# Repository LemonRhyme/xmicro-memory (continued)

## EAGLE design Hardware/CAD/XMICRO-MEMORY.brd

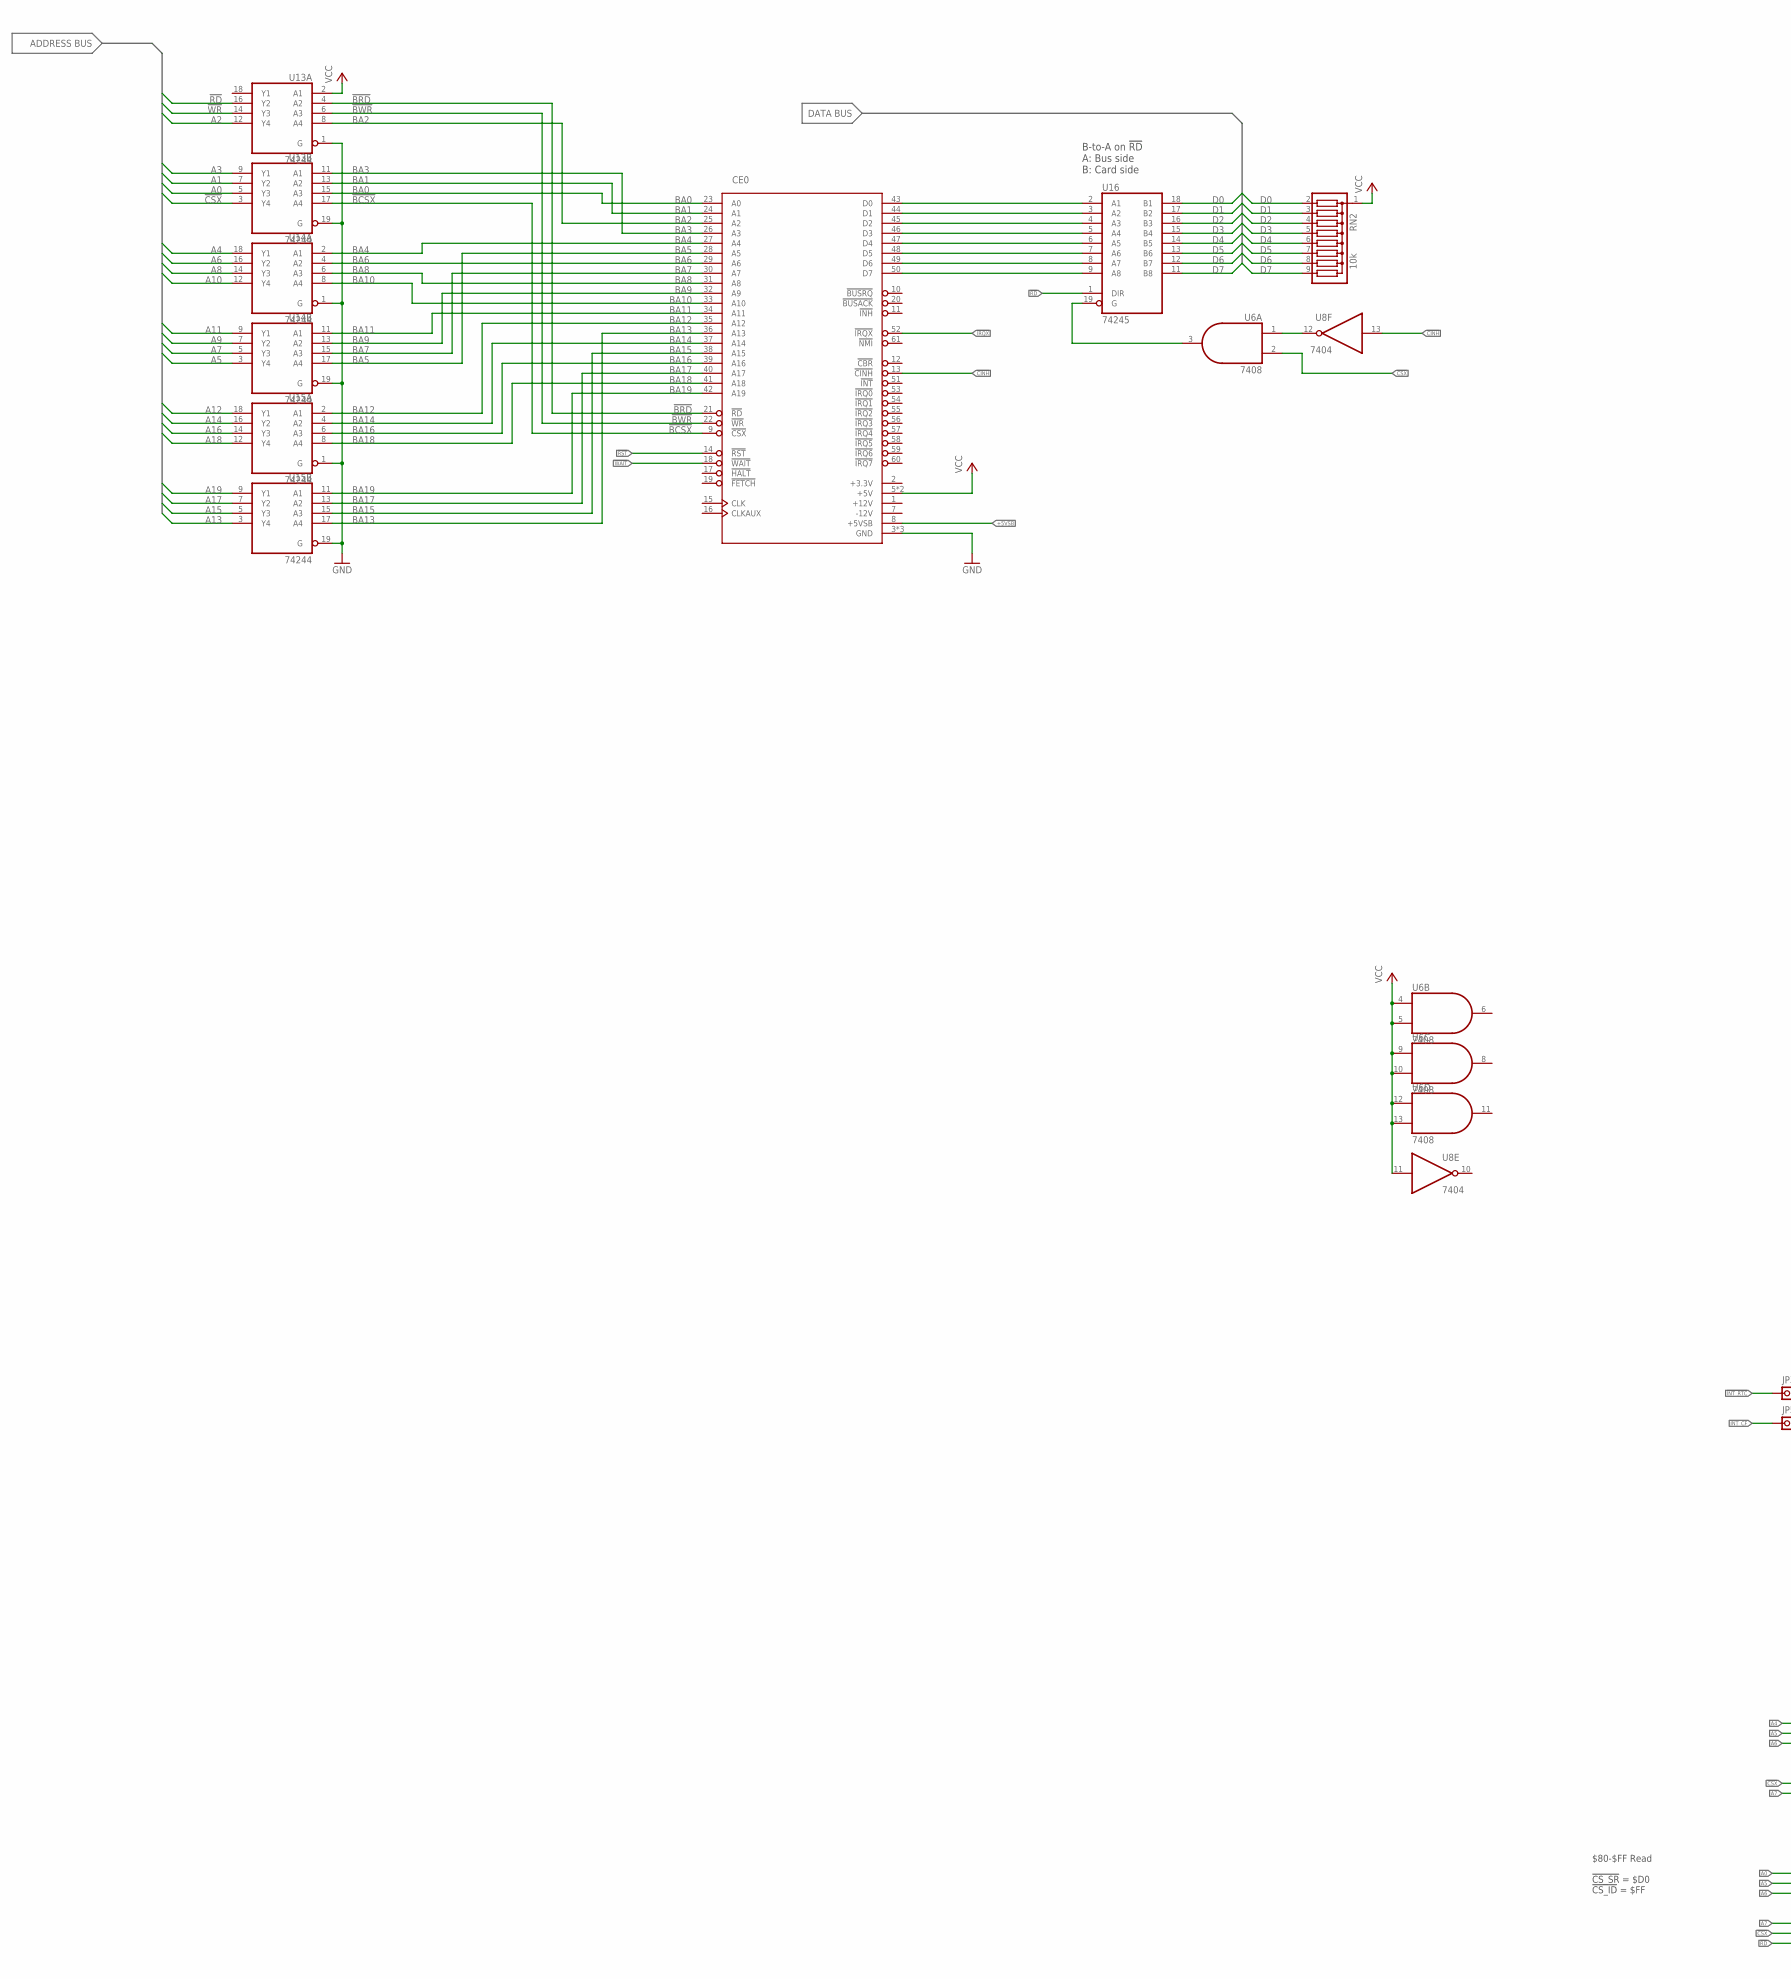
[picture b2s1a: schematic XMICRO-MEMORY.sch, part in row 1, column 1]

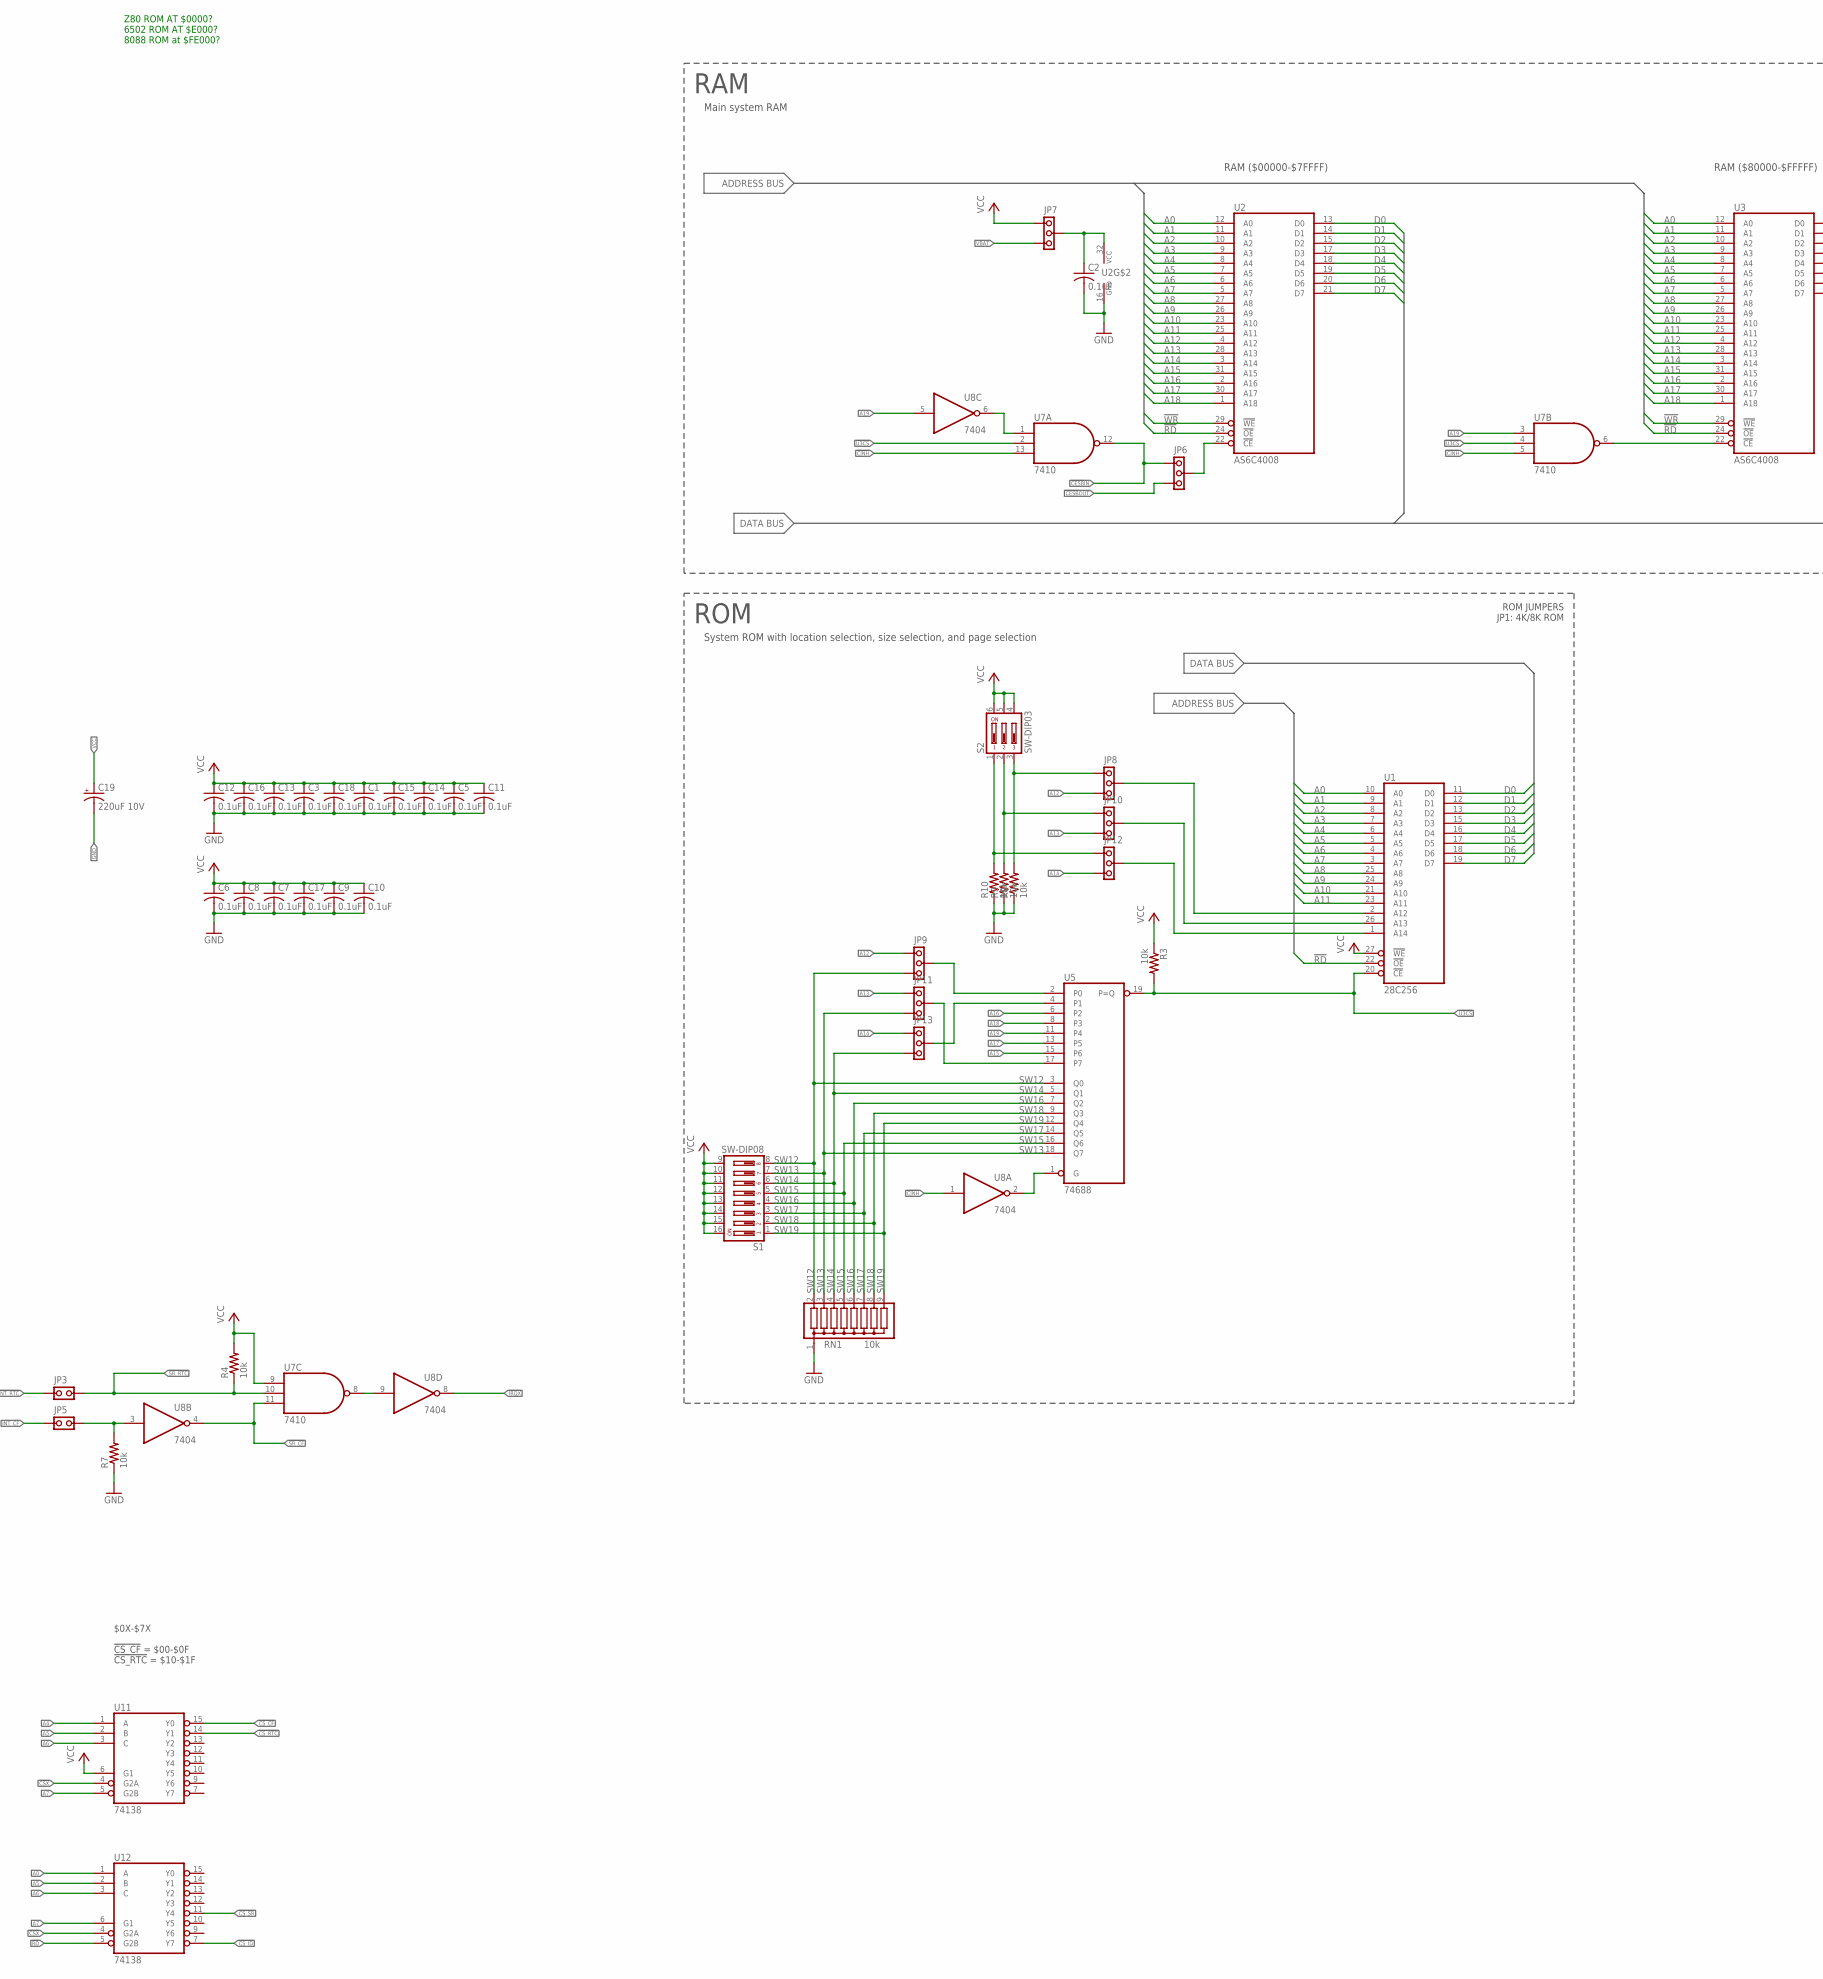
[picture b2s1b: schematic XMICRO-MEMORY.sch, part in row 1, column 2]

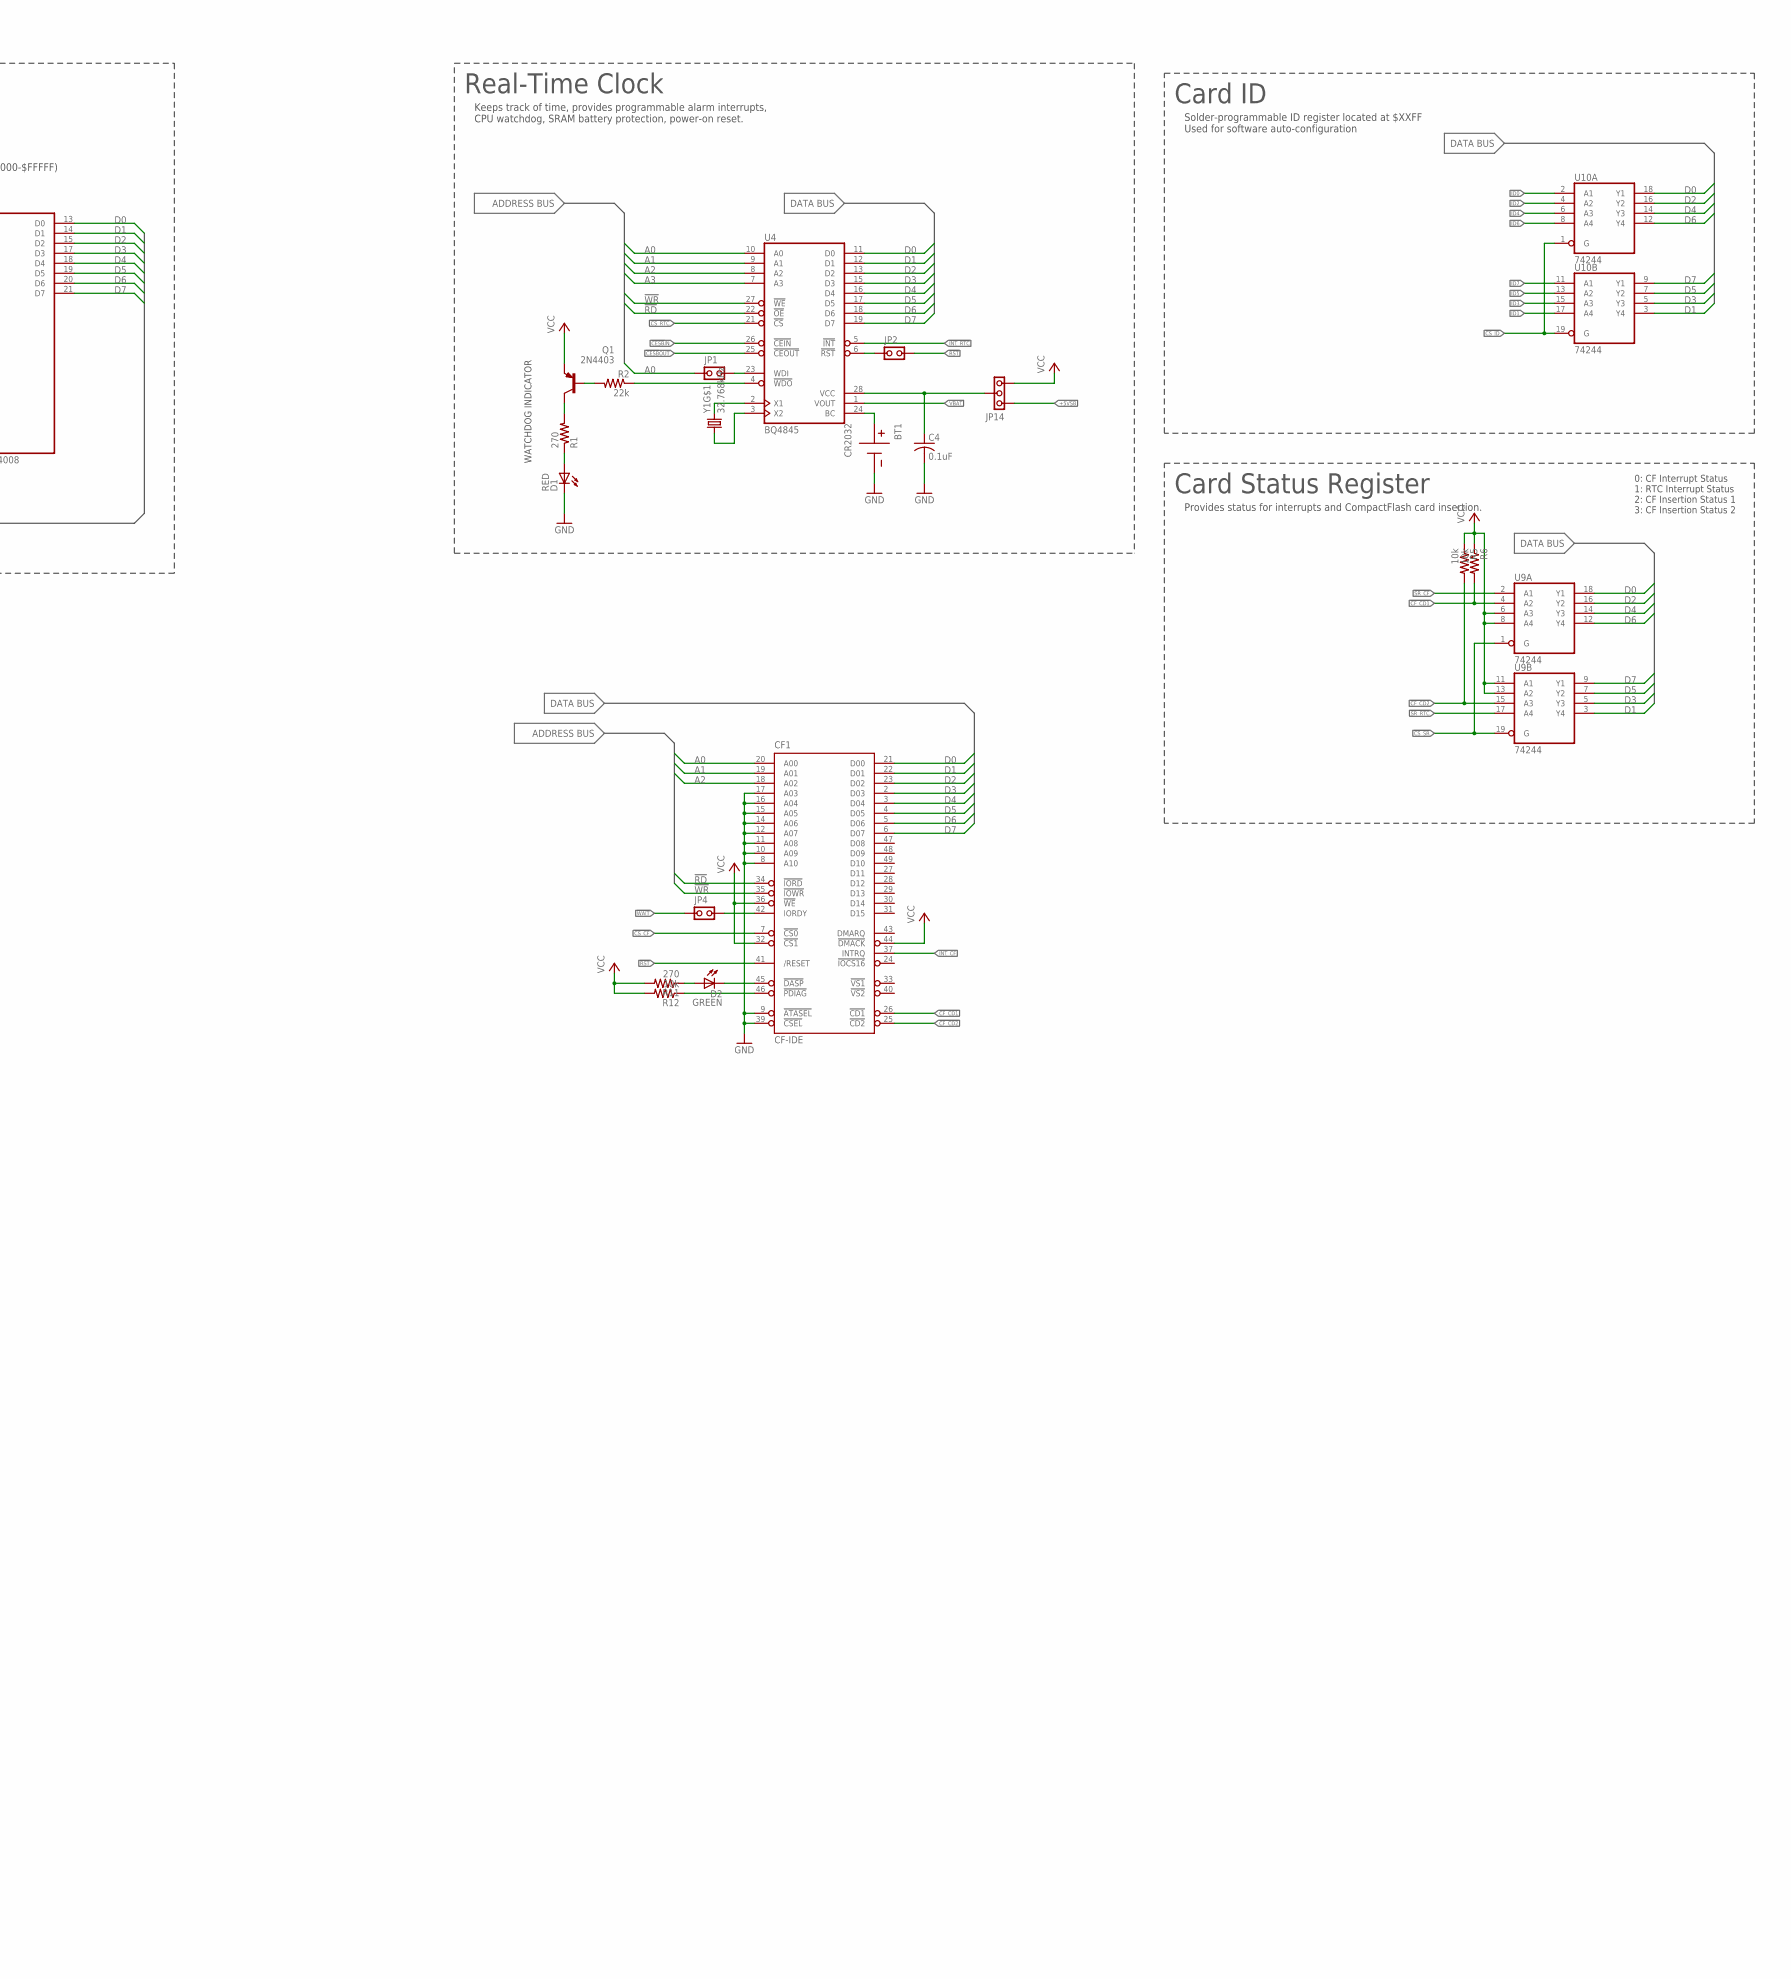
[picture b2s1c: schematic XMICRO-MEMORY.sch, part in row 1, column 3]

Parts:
BT1: CR2032; SMTU2032
C1, C2, C3, C4, C5, C6, C7, C8, C9, C10, C11, C12, C13, C14, C15, C16, C17, C18: 0.1uF; C025-024X044
C19: 220uF 10V; C-10-5
CE0: XMICRO-BUS-EDGE62M; EDGE62M
CF1: CF-IDE; CF-KYOCERA
D1: RED; LED5MM
D2: GREEN; LED-3-R
JP1, JP2, JP3, JP4, JP5: PINHD-1X2THRU; 1X02
JP6, JP7, JP8, JP9, JP10, JP11, JP12, JP13, JP14: PINHD1X3THRU; 1X03
Q1: 2N4403; TO92
R1, R11: 270; 0207/10
R2: 22k; 0207/10
R3, R4, R5, R6, R7, R8, R9, R10, R12: 10k; 0207/10
RN1, RN2: 10k; SIL9
S1: SW-DIP08; SW-DIP8
S2: SW-DIP03; SW-DIP3
U1: 28C256; 228-1277-00
U2, U3: AS6C4008; DIL32-6
U4: BQ4845; DIL28
U5: 74688; DIL20
U6: 7408; DIL14
U7: 7410; DIL14
U8: 7404; DIL14
U9, U10, U13, U14, U15: 74244; DIL20
U11, U12: 74138; DIL16
U16: 74245; DIL20
Y1: 32.768kHz; CRYSTAL-3X8H

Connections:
!BCSX: CE0.9 (!CSX), U13.17 (A4)
!BRD: CE0.21 (!RD), U13.4 (A2)
!BWR: CE0.22 (!WR), U13.6 (A3)
!CESB!IN: JP6.1, U4.26 (!CEIN), U7.12 (O)
!CESB!OUT: JP6.3, U4.25 (!CEOUT)
!CF_CD1: CF1.26 (!CD1), R6.2, U9.4 (A2)
!CF_CD2: CF1.25 (!CD2), R5.2, U9.15 (A3)
!CINH: CE0.13 (!CINH), U7.5 (I2), U7.13 (I2), U8.1 (I), U8.13 (I)
!CSX: U6.2 (I1), U11.4 (G2A), U12.4 (G2A), U13.3 (Y4)
!CS_CF: CF1.7 (!CS0), U11.15 (Y0)
!CS_ID: U10.1 (G), U10.19 (G), U12.7 (Y7)
!CS_RTC: U4.21 (!CS), U11.14 (Y1)
!CS_SR: U9.1 (G), U9.19 (G), U12.11 (Y4)
!INT_RTC: JP3.1, U4.5 (!INT)
!IRQX: CE0.52 (!IRQX), U8.8 (O)
!RD: CF1.34 (!IORD), U1.22 (!OE), U2.24 (!OE), U3.24 (!OE), U4.22 (!OE), U12.5 (G2B), U13.16 (Y2), U16.1 (DIR)
!RST: CE0.14 (!RST), CF1.41 (/RESET), JP2.2
!SR_CF: U7.11 (I2), U8.4 (O), U9.2 (A1)
!SR_RTC: JP3.2, R4.1, U7.10 (I1), U9.17 (A4)
!U1CS: JP6.2, U2.22 (!CE)
!U2CS: U3.22 (!CE), U7.6 (O)
!U3CS: R3.2, U1.20 (!CE), U5.19 (P=Q), U7.2 (I1), U7.4 (I1)
!WAIT: CE0.18 (!WAIT), JP4.1
!WR: CF1.35 (!IOWR), U2.29 (!WE), U3.29 (!WE), U4.27 (!WE), U13.14 (Y3)
+5VSB: CE0.8 (+5VSB), JP14.1
A0: CF1.20 (A00), JP1.1, U1.10 (A0), U2.12 (A0), U3.12 (A0), U4.10 (A0), U12.1 (A), U13.5 (Y3)
A1: CF1.19 (A01), U1.9 (A1), U2.11 (A1), U3.11 (A1), U4.9 (A1), U13.7 (Y2)
A2: CF1.18 (A02), U1.8 (A2), U2.10 (A2), U3.10 (A2), U4.8 (A2), U13.12 (Y4)
A3: U1.7 (A3), U2.9 (A3), U3.9 (A3), U4.7 (A3), U13.9 (Y1)
A4: U1.6 (A4), U2.8 (A4), U3.8 (A4), U11.1 (A), U14.18 (Y1)
A5: U1.5 (A5), U2.7 (A5), U3.7 (A5), U11.2 (B), U12.2 (B), U14.3 (Y4)
A6: U1.4 (A6), U2.6 (A6), U3.6 (A6), U11.3 (C), U12.3 (C), U14.16 (Y2)
A7: U1.3 (A7), U2.5 (A7), U3.5 (A7), U11.5 (G2B), U12.6 (G1), U14.5 (Y3)
A8: U1.25 (A8), U2.27 (A8), U3.27 (A8), U14.14 (Y3)
A9: U1.24 (A9), U2.26 (A9), U3.26 (A9), U14.7 (Y2)
A10: U1.21 (A10), U2.23 (A10), U3.23 (A10), U14.12 (Y4)
A11: U1.23 (A11), U2.25 (A11), U3.25 (A11), U14.9 (Y1)
A12: JP8.3, JP9.1, U2.4 (A12), U3.4 (A12), U15.18 (Y1)
A13: JP10.3, JP11.1, U2.28 (A13), U3.28 (A13), U15.3 (Y4)
A14: JP12.3, JP13.1, U2.3 (A14), U3.3 (A14), U15.16 (Y2)
A15: U2.31 (A15), U3.31 (A15), U5.15 (P6), U15.5 (Y3)
A16: U2.2 (A16), U3.2 (A16), U5.6 (P2), U15.14 (Y3)
A17: U2.30 (A17), U3.30 (A17), U5.13 (P5), U15.7 (Y2)
A18: U2.1 (A18), U3.1 (A18), U5.8 (P3), U15.12 (Y4)
A19: U5.11 (P4), U7.3 (I0), U8.5 (I), U15.9 (Y1)
BA0: CE0.23 (A0), U13.15 (A3)
BA1: CE0.24 (A1), U13.13 (A2)
BA2: CE0.25 (A2), U13.8 (A4)
BA3: CE0.26 (A3), U13.11 (A1)
BA4: CE0.27 (A4), U14.2 (A1)
BA5: CE0.28 (A5), U14.17 (A4)
BA6: CE0.29 (A6), U14.4 (A2)
BA7: CE0.30 (A7), U14.15 (A3)
BA8: CE0.31 (A8), U14.6 (A3)
BA9: CE0.32 (A9), U14.13 (A2)
BA10: CE0.33 (A10), U14.8 (A4)
BA11: CE0.34 (A11), U14.11 (A1)
BA12: CE0.35 (A12), U15.2 (A1)
BA13: CE0.36 (A13), U15.17 (A4)
BA14: CE0.37 (A14), U15.4 (A2)
BA15: CE0.38 (A15), U15.15 (A3)
BA16: CE0.39 (A16), U15.6 (A3)
BA17: CE0.40 (A17), U15.13 (A2)
BA18: CE0.41 (A18), U15.8 (A4)
BA19: CE0.42 (A19), U15.11 (A1)
D0: CF1.21 (D00), RN2.2, U1.11 (D0), U2.13 (D0), U3.13 (D0), U4.11 (D0), U9.18 (Y1), U10.18 (Y1), U16.18 (B1)
D1: CF1.22 (D01), RN2.3, U1.12 (D1), U2.14 (D1), U3.14 (D1), U4.12 (D1), U9.3 (Y4), U10.3 (Y4), U16.17 (B2)
D2: CF1.23 (D02), RN2.4, U1.13 (D2), U2.15 (D2), U3.15 (D2), U4.13 (D2), U9.16 (Y2), U10.16 (Y2), U16.16 (B3)
D3: CF1.2 (D03), RN2.5, U1.15 (D3), U2.17 (D3), U3.17 (D3), U4.15 (D3), U9.5 (Y3), U10.5 (Y3), U16.15 (B4)
D4: CF1.3 (D04), RN2.6, U1.16 (D4), U2.18 (D4), U3.18 (D4), U4.16 (D4), U9.14 (Y3), U10.14 (Y3), U16.14 (B5)
D5: CF1.4 (D05), RN2.7, U1.17 (D5), U2.19 (D5), U3.19 (D5), U4.17 (D5), U9.7 (Y2), U10.7 (Y2), U16.13 (B6)
D6: CF1.5 (D06), RN2.8, U1.18 (D6), U2.20 (D6), U3.20 (D6), U4.18 (D6), U9.12 (Y4), U10.12 (Y4), U16.12 (B7)
D7: CF1.6 (D07), RN2.9, U1.19 (D7), U2.21 (D7), U3.21 (D7), U4.19 (D7), U9.9 (Y1), U10.9 (Y1), U16.11 (B8)
GND: BT1.-, C1.2, C2.2, C3.2, C4.2, C5.2, C6.2, C7.2, C8.2, C9.2, C10.2, C11.2, C12.2, C13.2, C14.2, C15.2, C16.2, C17.2, C18.2, C19.-, CE0.3 (GND), CE0.4 (GND), CE0.62 (GND), CF1.1 (GND), CF1.8 (A10), CF1.9 (!ATASEL), CF1.10 (A09), CF1.11 (A08), CF1.12 (A07), CF1.14 (A06), CF1.15 (A05), CF1.16 (A04), CF1.17 (A03), CF1.39 (!CSEL), CF1.50 (GND), CF1.P$51 (GND), CF1.P$52 (GND), D1.K (C), R7.1, R8.1, R9.1, R10.1, RN1.1, U1.14 (GND), U2.16 (GND), U3.16 (GND), U4.14 (GND), U4.20 (GND), U5.10 (GND), U6.7 (GND), U7.7 (GND), U8.7 (GND), U9.10 (GND), U10.10 (GND), U11.8 (GND), U12.8 (GND), U13.1 (G), U13.10 (GND), U13.19 (G), U14.1 (G), U14.10 (GND), U14.19 (G), U15.1 (G), U15.10 (GND), U15.19 (G), U16.10 (GND), Y1.P$1 (GND)
ID0: U10.2 (A1)
ID1: U10.17 (A4)
ID2: U10.4 (A2)
ID3: U10.15 (A3)
ID4: U10.6 (A3)
ID5: U10.13 (A2)
ID6: U10.8 (A4)
ID7: U10.11 (A1)
INT_CF: CF1.37 (INTRQ), JP5.1
unnamed: CF1.45 (!DASP), D2.C
unnamed: D2.A, R11.1
unnamed: CF1.42 (IORDY), JP4.2
unnamed: U5.1 (G), U8.2 (O)
unnamed: U4.3 (X2), Y1.1
unnamed: U4.2 (X1), Y1.2
unnamed: BT1.+, U4.24 (BC)
unnamed: Q1.2 (B), R2.2
unnamed: C2.1, JP7.2, U2.32 (VCC)
unnamed: Q1.3 (C), R1.2
unnamed: JP1.2, U4.23 (WDI)
unnamed: JP10.2, U1.26 (A13)
unnamed: D1.A, R1.1
unnamed: R2.1, U4.4 (!WDO)
unnamed: JP8.2, U1.2 (A12)
unnamed: JP12.2, U1.1 (A14)
unnamed: JP13.2, U5.4 (P1)
unnamed: U7.8 (O), U8.9 (I)
unnamed: U6.1 (I0), U8.12 (O)
unnamed: JP5.2, R7.2, U8.3 (I)
unnamed: JP11.2, U5.17 (P7)
unnamed: JP9.2, U5.2 (P0)
unnamed: C4.1, JP14.2, U4.28 (VCC)
unnamed: CF1.46 (!PDIAG), R12.1
unnamed: U7.1 (I0), U8.6 (O)
unnamed: JP2.1, U4.6 (!RST)
unnamed: U6.3 (O), U16.19 (G)
unnamed: CE0.50 (D7), U16.9 (A8)
unnamed: CE0.49 (D6), U16.8 (A7)
unnamed: CE0.48 (D5), U16.7 (A6)
unnamed: CE0.47 (D4), U16.6 (A5)
unnamed: CE0.46 (D3), U16.5 (A4)
unnamed: CE0.45 (D2), U16.4 (A3)
unnamed: CE0.44 (D1), U16.3 (A2)
unnamed: CE0.43 (D0), U16.2 (A1)
unnamed: JP8.1, R8.2, S2.3
unnamed: JP10.1, R9.2, S2.2
unnamed: JP12.1, R10.2, S2.1
SW12: JP9.3, RN1.2, S1.8, U5.3 (Q0)
SW13: JP11.3, RN1.3, S1.7, U5.18 (Q7)
SW14: JP13.3, RN1.4, S1.6, U5.5 (Q1)
SW15: RN1.5, S1.5, U5.16 (Q6)
SW16: RN1.6, S1.4, U5.7 (Q2)
SW17: RN1.7, S1.3, U5.14 (Q5)
SW18: RN1.8, S1.2, U5.9 (Q3)
SW19: RN1.9, S1.1, U5.12 (Q4)
VBAT: JP7.3, U4.1 (VOUT)
VCC: C1.1, C3.1, C5.1, C6.1, C7.1, C8.1, C9.1, C10.1, C11.1, C12.1, C13.1, C14.1, C15.1, C16.1, C17.1, C18.1, C19.+, CE0.5 (+5V), CE0.6 (+5V), CF1.13 (VCC), CF1.32 (!CS1), CF1.36 (!WE), CF1.38 (VCC), CF1.44 (!DMACK), JP7.1, JP14.3, Q1.1 (E), R3.1, R4.2, R5.1, R6.1, R11.2, R12.2, RN2.1, S1.9, S1.10, S1.11, S1.12, S1.13, S1.14, S1.15, S1.16, S2.4, S2.5, S2.6, U1.27 (!WE), U1.28 (VCC), U3.32 (VCC), U5.20 (VCC), U6.4 (I0), U6.5 (I1), U6.9 (I0), U6.10 (I1), U6.12 (I0), U6.13 (I1), U6.14 (VCC), U7.9 (I0), U7.14 (VCC), U8.11 (I), U8.14 (VCC), U9.6 (A3), U9.8 (A4), U9.11 (A1), U9.13 (A2), U9.20 (VCC), U10.20 (VCC), U11.6 (G1), U11.16 (VCC), U12.16 (VCC), U13.2 (A1), U13.20 (VCC), U14.20 (VCC), U15.20 (VCC), U16.20 (VCC)

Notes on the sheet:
RAM
Main system RAM
Z80 ROM AT $0000? 6502 ROM AT $E000? 8088 ROM at $FE000?
ADDRESS BUS
DATA BUS
RAM ($00000-$7FFFF)
RAM ($80000-$FFFFF)
WATCHDOG INDICATOR
Real-Time Clock
Keeps track of time, provides programmable alarm interrupts, CPU watchdog, SRAM battery protection, power-on reset.
ROM
System ROM with location selection, size selection, and page selection
ROM JUMPERS JP1: 4K/8K ROM
$0X-$7X !CS_CF! = $00-$0F !CS_RTC! = $10-$1F
Card ID
Solder-programmable ID register located at $XXFF Used for software auto-configuration
B-to-A on !RD! A: Bus side B: Card side
Card Status Register
Provides status for interrupts and CompactFlash card insertion.
0: CF Interrupt Status 1: RTC Interrupt Status 2: CF Insertion Status 1 3: CF Insertion Status 2
$80-$FF Read !CS_SR! = $D0 !CS_ID! = $FF

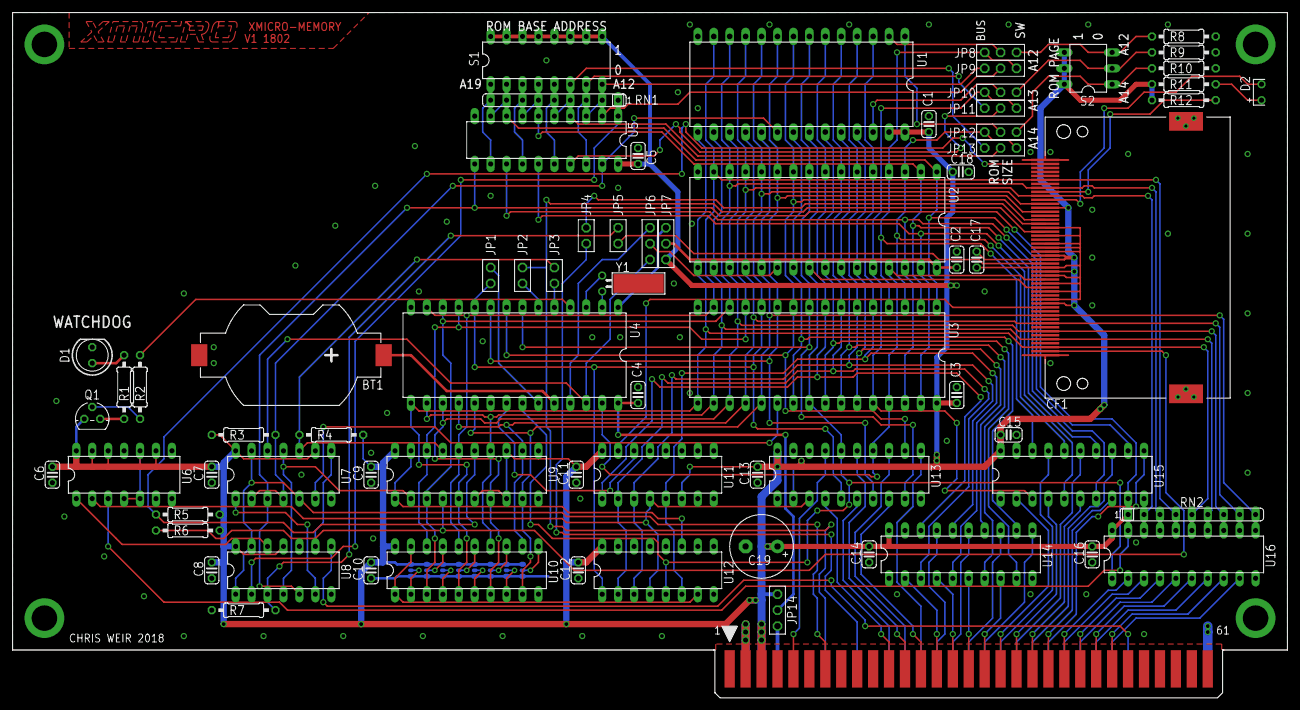
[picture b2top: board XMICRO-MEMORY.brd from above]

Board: 2 copper layers, 203.2 x 109.2 mm, 72 parts (0 on the bottom side), 123 nets.

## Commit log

2018-08-16 Updated the name in the license
2019-05-28 Updated schematic xrefs to indicate signal direction.
2019-05-28 Updated directory structure
2020-08-29 Added picture and updated README.md
2024-09-15 Updated to Gen 2 V1.0
2024-09-29 Updated datasheet formatting
2024-09-30 Updated datasheet template
